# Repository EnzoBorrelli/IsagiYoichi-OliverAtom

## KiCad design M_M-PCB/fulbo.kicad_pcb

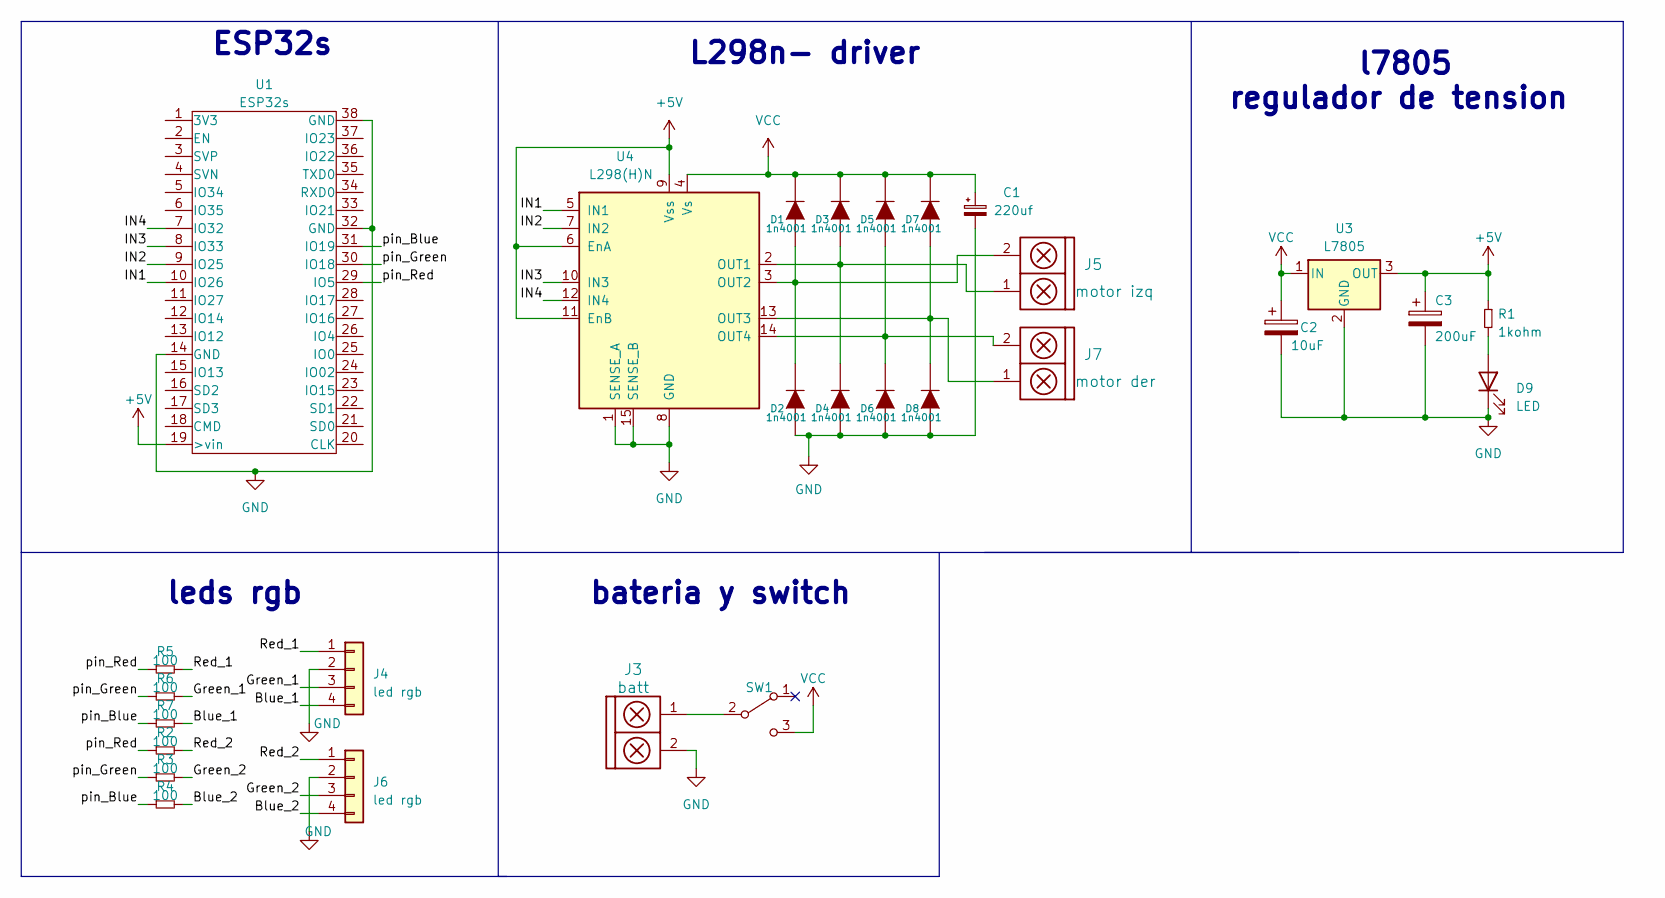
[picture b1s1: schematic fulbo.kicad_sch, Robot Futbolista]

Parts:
C1: 220uf; CP_Radial_D5.0mm_P2.00mm
C2: 10uF; CAP_0.1
C3: 200uF; CAP_0.1
D1, D2, D3, D4, D5, D6, D7, D8: 1n4001; DO-41
D9: LED; Pin_Header_2
J3: batt; BORNERA2_AZUL
J4, J6: led rgb; pin_strip_4
J5: motor izq; BORNERA2_AZUL
J7: motor der; BORNERA2_AZUL
R1: 1kohm; RES0.3
R2, R3, R4, R5, R6, R7: 100; RES0.3
SW1: SW_SPDT; SW_SPDT_TH_Vertical
U1: ESP32s; ESP32S
U3: L7805; to220
U4: L298(H)N; TO-220-15_P2.54x2.54mm_StaggerEven_Lead4.58mm_Vertical

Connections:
+5V: C3.1, R1.1, U1.19 (>vin), U3.3 (OUT), U4.6 (EnA), U4.9 (Vss), U4.11 (EnB)
/Blue_1: J4.4, R7.2
/Blue_2: J6.4, R4.2
/Green_1: J4.3, R6.2
/Green_2: J6.3, R3.2
/IN1: U1.10 (IO26), U4.5 (IN1)
/IN2: U1.9 (IO25), U4.7 (IN2)
/IN3: U1.8 (IO33), U4.10 (IN3)
/IN4: U1.7 (IO32), U4.12 (IN4)
/Red_1: J4.1, R5.2
/Red_2: J6.1, R2.2
/pin_Blue: R4.1, R7.1, U1.31 (IO19)
/pin_Green: R3.1, R6.1, U1.30 (IO18)
/pin_Red: R2.1, R5.1, U1.29 (IO5)
GND: C1.2, C2.2, C3.2, D2.1 (A), D4.1 (A), D6.1 (A), D8.1 (A), D9.1 (K), J3.2, J4.2, J6.2, U1.14 (GND), U1.32 (GND), U1.38 (GND), U3.2 (GND), U4.1 (SENSE_A), U4.8 (GND), U4.15 (SENSE_B)
unnamed: D1.1 (A), D2.2 (K), J5.2, U4.3 (OUT2)
unnamed: D3.1 (A), D4.2 (K), J5.1, U4.2 (OUT1)
unnamed: D5.1 (A), D6.2 (K), J7.2, U4.14 (OUT4)
unnamed: D7.1 (A), D8.2 (K), J7.1, U4.13 (OUT3)
unnamed: D9.2 (A), R1.2
unnamed: J3.1, SW1.2 (B)
VCC: C1.1, C2.1, D1.2 (K), D3.2 (K), D5.2 (K), D7.2 (K), SW1.3 (C), U3.1 (IN), U4.4 (Vs)

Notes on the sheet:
leds rgb
l7805 regulador de tension
L298n- driver
bateria y switch
ESP32s

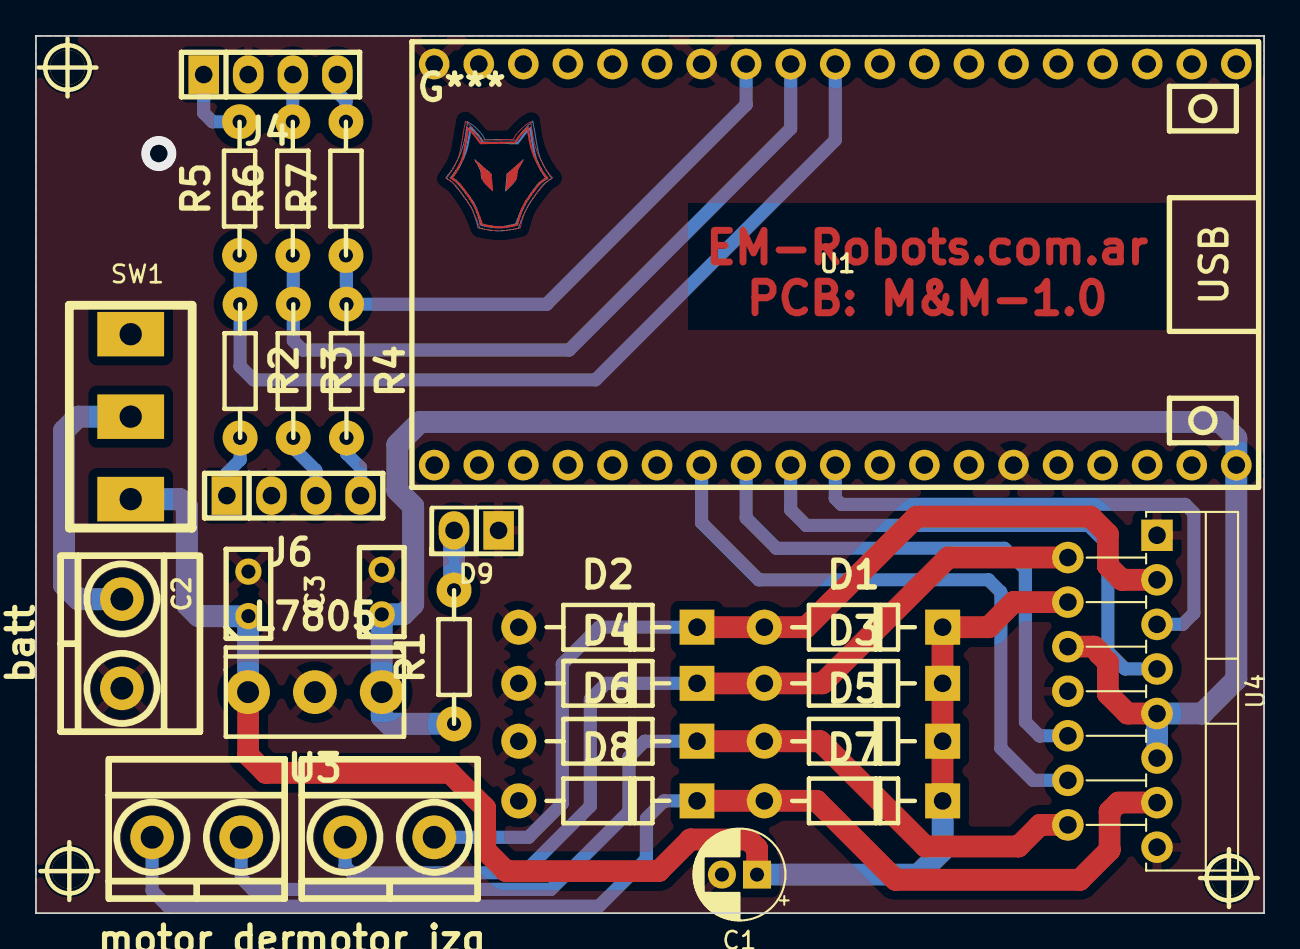
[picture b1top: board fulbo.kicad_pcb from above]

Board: 2 copper layers, 70.0 x 50.0 mm, 31 parts (0 on the bottom side), 22 nets.

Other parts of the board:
hole_2mm, hole_2mm#2, hole_2mm#3: VAL**; hole_2mm

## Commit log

2023-07-02 mucho texto
2023-07-03 up to date
